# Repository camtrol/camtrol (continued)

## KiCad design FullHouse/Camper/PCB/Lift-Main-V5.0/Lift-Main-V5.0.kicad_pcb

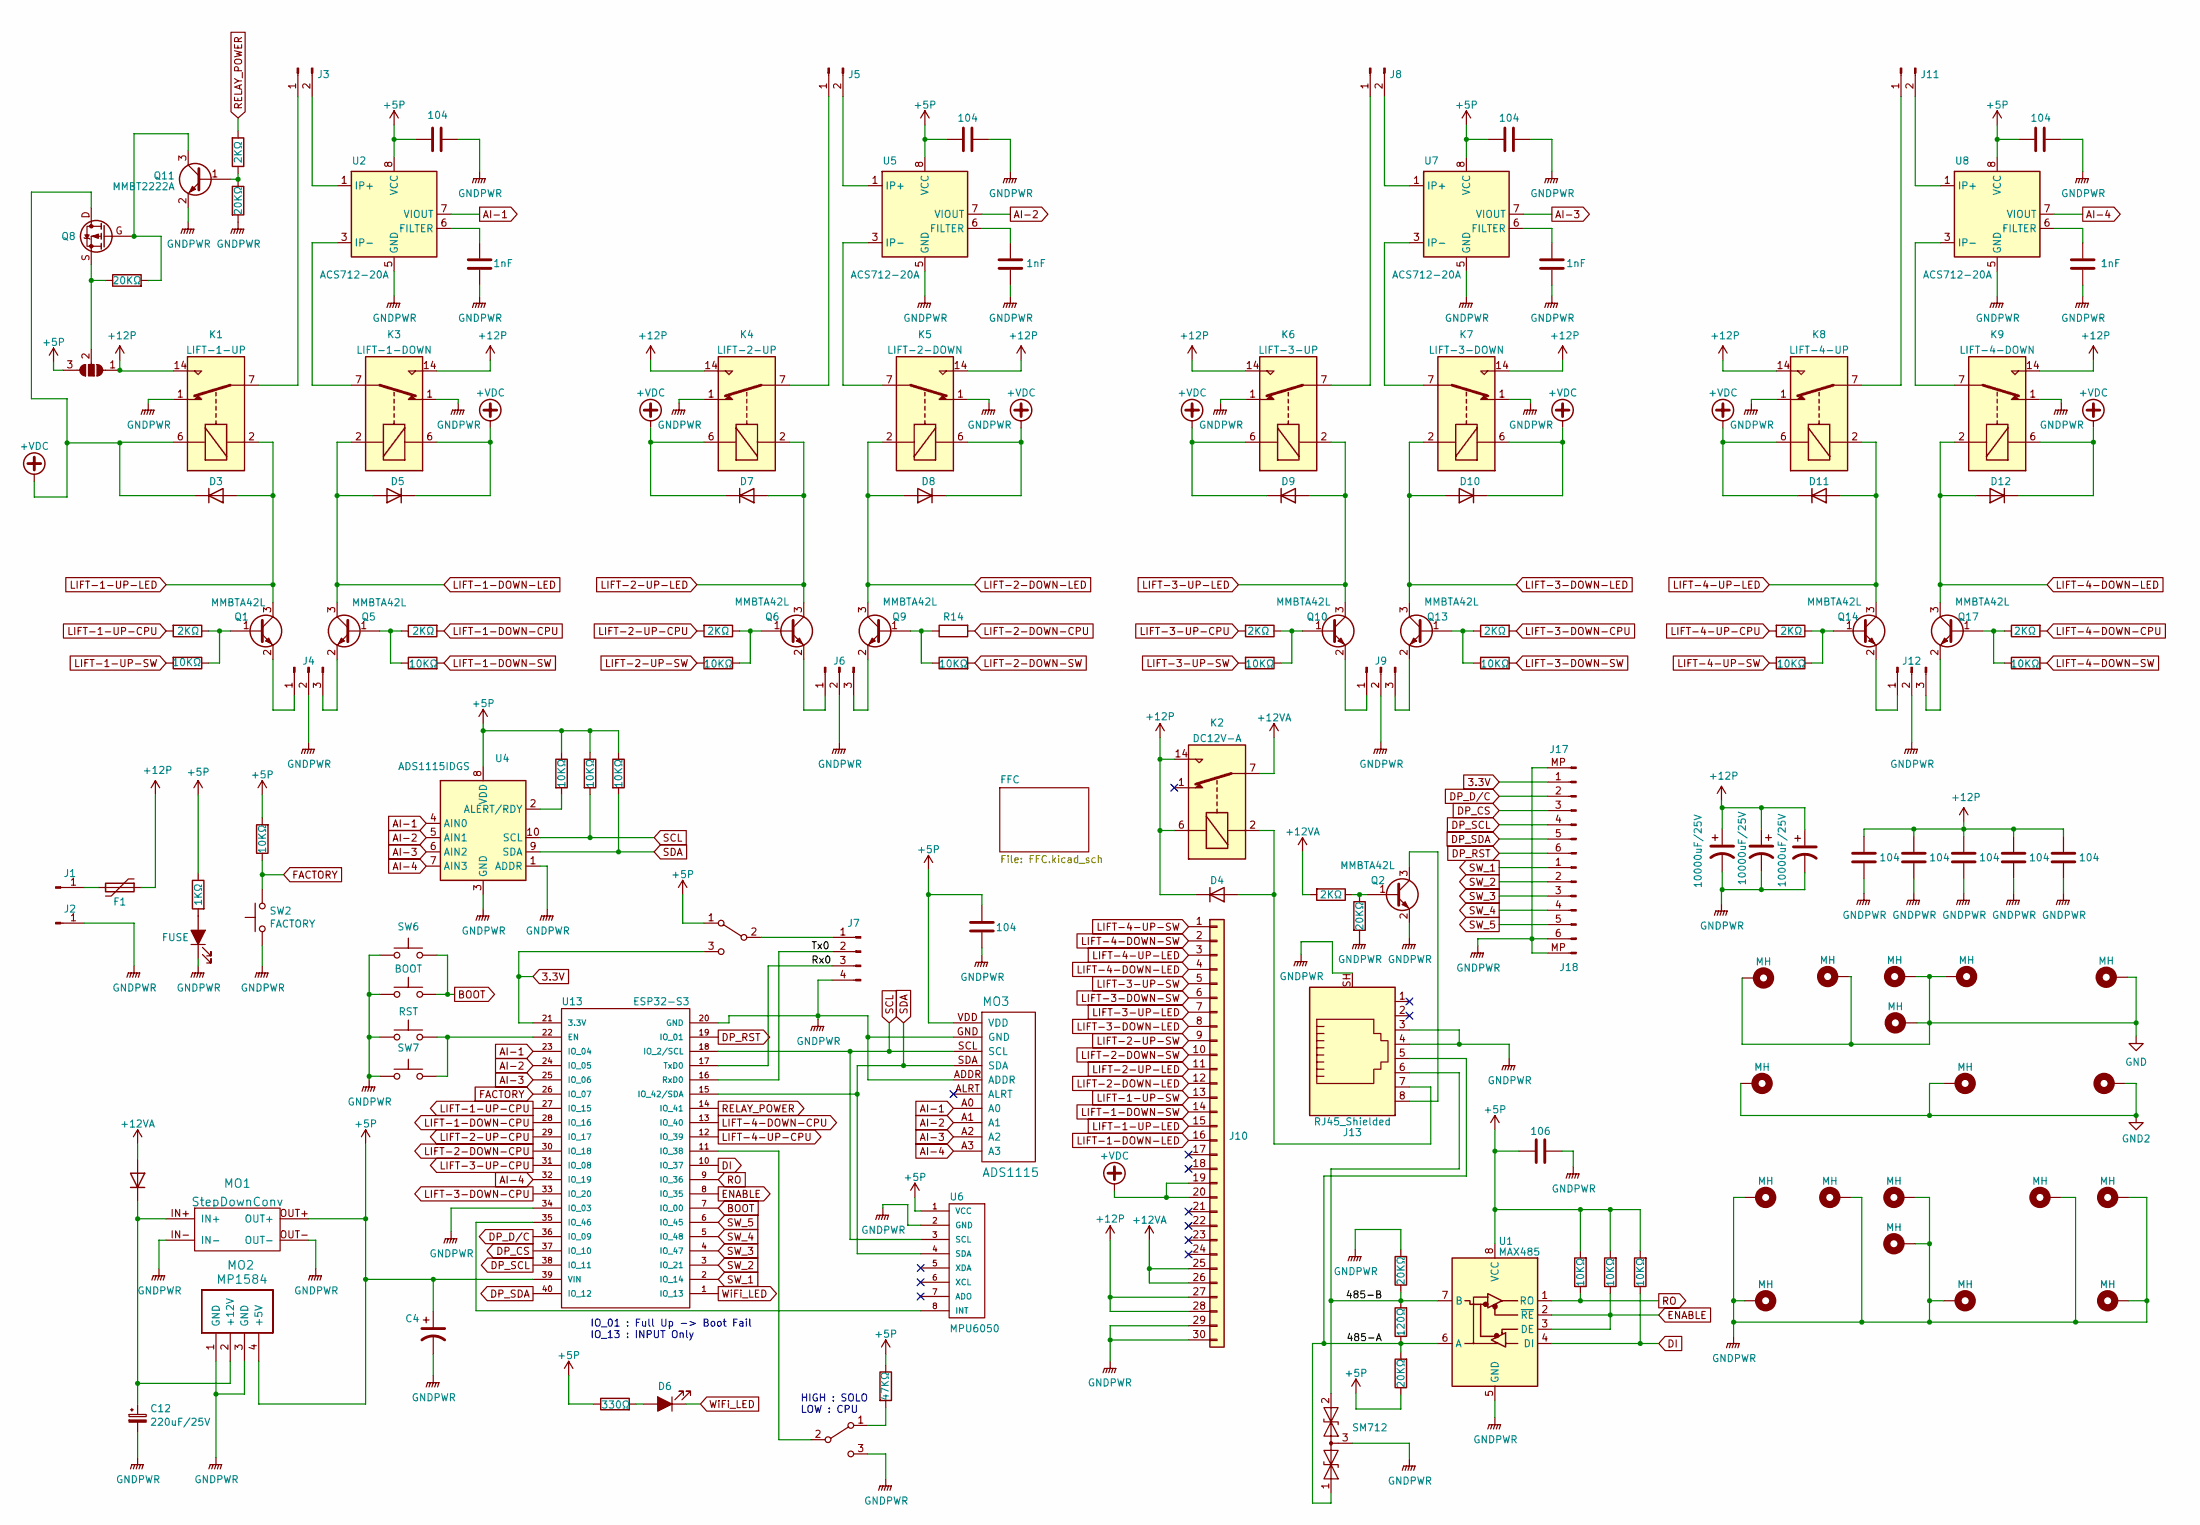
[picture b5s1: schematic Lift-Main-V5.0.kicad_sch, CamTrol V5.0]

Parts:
C2, C5, C6, C8, C11, C13, C14, C15, C16, C17: 104; C_0805_HandSoldering
C3, C7, C9, C19: 1nF; C_0805_HandSoldering
C4: 100uF; CP_Elec_6.3x5.3
C10, C18, C20: 10000uF/25V; CP_Radial_D18.0mm_P7mm
C12: 220uF/25V; CP_Radial_D8.0mm_P2.50mm
C21: 106; C_0805_HandSoldering
D1: SS34; D_SMA
D2: FUSE; LED_0805
D3, D5, D7, D8, D9, D10, D11, D12: type="D" model="1N4148W" lib=""; D_SOD-123
D4: 1N4148W; D_SOD-123
D6: RED LED; LED_0805
D13: SM712; SOT-23
F1: FRG500-16F; FUSE-PIN-Holder
H1, H3, H4, H5, H6, H9, H10, H11, H13, H15, H16, H17, H18, H19, H20, H22, H24, H25: MH; MountingHole_3.2mm_M3-support
J1, J2: BR-120
J3, J5, J8, J11: Conn_01x02_Male; BR-1300C-2P
J4, J6, J9, J12: Conn_01x03_Male; USL-5SAB2-3P
J7: 5267-04P; Molex_SPOX_5267-04A_1x04_P2.50mm_Vertical
J10: Conn_01x30; IDC-Header_2x15_P2.54mm_Vertical
J13: RJ45_Shielded; RJ45_8P_OPEN
J17, J18: Conn_01x06_Pin; JST_GH_SM06B-GHS-TB_1x06-1MP_P1.25mm_Horizontal
JP2: SolderJumper_3_Open; SolderJumper-3_P1.3mm_Open_RoundedPad1.0x1.5mm
K1: LIFT-1-UP; JQC-T78-DC12V-C
K2: DC12V-A; JQC-T78-DC12V-C
K3: LIFT-1-DOWN; JQC-T78-DC12V-C
K4: LIFT-2-UP; JQC-T78-DC12V-C
K5: LIFT-2-DOWN; JQC-T78-DC12V-C
K6: LIFT-3-UP; JQC-T78-DC12V-C
K7: LIFT-3-DOWN; JQC-T78-DC12V-C
K8: LIFT-4-UP; JQC-T78-DC12V-C
K9: LIFT-4-DOWN; JQC-T78-DC12V-C
MO1: StepDownConv; LM2596 DC-DC
MO2: MP1584; MP1584-SMD
MO3: ADS1115
Q1, Q2, Q5, Q6, Q9, Q10, Q13, Q14, Q17: MMBTA42L; SOT-23
Q8: AOD4185; AOD1485
Q11: MMBT2222A; SOT-23
R1, R5, R9, R12, R13, R15, R16, R18, R20, R22, R23, R25, R26, R28, R29: 10KΩ; R_0805_HandSoldering
R2, R7, R11, R17, R21, R24, R27, R30, R38: 2KΩ; R_0805_HandSoldering
R3, R14: 1KΩ; R_0805_HandSoldering
R4, R8, R31, R36, R37: 20KΩ; R_0805_HandSoldering
R6: 120Ω; R_0805_HandSoldering
R10: 330Ω; R_0805_HandSoldering
R19: 47KΩ; R_0805_HandSoldering
SW1, SW3: NW3-SK-02
SW2: FACTORY; SW_Tactile_SKHH_Angled
SW4: RST; SW_SPST_CK_RS282G05A3
SW5: BOOT; SW_SPST_CK_RS282G05A3
SW6, SW7: SW_Push; TS-3404
U1: MAX485; SOIC-8_3.9x4.9mm_P1.27mm
U2, U5, U7, U8: ACS712-20A; SOIC-8_3.9x4.9mm_P1.27mm
U4: ADS1115IDGS; TSSOP-10_3x3mm_P0.5mm
U6: MPU6050
U13: ESP32-S3

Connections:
3.3V: J17.1 (Pin_2), SW3.3 (C), U13.21 (3.3V)
+5P: C2.1, C4.1, C5.2, C6.1, C8.1, C16.1, C21.1, JP2.3 (B), MO1.OUT+, MO2.4 (+5V), MO3.VDD, R1.1, R3.1, R8.1, R9.2, R10.1, R12.2, R13.2, R15.1, R19.1, R28.2, R29.1, SW3.1 (A), U1.8 (VCC), U2.8 (VCC), U4.8 (VDD), U5.8 (VCC), U6.1 (VCC), U7.8 (VCC), U8.8 (VCC), U13.39 (VIN); also elsewhere on the board
+12P: C10.1, C11.1, C13.1, C14.1, C15.1, C17.1, C18.1, C20.1, D4.2 (K), F1.1, J10.27, J10.28, JP2.1 (A), K1.14, K2.6, K2.14, K3.14, K4.14, K5.14, K6.14, K7.14, K8.14, K9.14; also elsewhere on the board
+12VA: D1.1 (A), J10.25, J10.26, K2.7, R30.2; also elsewhere on the board
+VDC: D3.2 (K), D5.2 (K), D7.2 (K), D8.2 (K), D9.2 (K), D10.2 (K), D11.2 (K), D12.2 (K), J10.19, J10.20, K1.6, K3.6, K4.6, K5.6, K6.6, K7.6, K8.6, K9.6, Q8.D (Drain); also elsewhere on the board
/485-A: D13.1 (A1), J13.5, R6.1, R8.2, U1.6 (A)
/485-B: D13.2 (A2), J13.6, R4.1, R6.2, U1.7 (B)
/Rx0: J7.3, U13.17 (TxD0)
/Tx0: J7.2, U13.16 (RxD0)
AI-1: MO3.A0, U2.7 (VIOUT), U4.4 (AIN0), U13.23 (IO_04); also elsewhere on the board
AI-2: MO3.A1, U4.5 (AIN1), U5.7 (VIOUT), U13.24 (IO_05); also elsewhere on the board
AI-3: MO3.A2, U4.6 (AIN2), U7.7 (VIOUT), U13.25 (IO_06); also elsewhere on the board
AI-4: MO3.A3, U4.7 (AIN3), U8.7 (VIOUT), U13.32 (IO_19); also elsewhere on the board
BOOT: SW5.2, SW6.2, U13.7 (IO_00)
DI: R13.1, U1.4 (DI), U13.10 (IO_37)
DP_CS: J17.3 (Pin_4), U13.37 (IO_10)
DP_D/C: J17.2 (Pin_3), U13.36 (IO_09)
DP_RST: J17.6 (Pin_7), U13.19 (IO_01)
DP_SCL: J17.4 (Pin_5), U13.38 (IO_11)
DP_SDA: J17.5 (Pin_6), U13.40 (IO_12)
ENABLE: R12.1, U1.2 (~RE), U1.3 (DE), U13.8 (IO_35)
FACTORY: R28.1, SW2.1, U13.26 (IO_07)
GND: H15.1, H16.1, H17.1, H18.1, H22.1, H24.1
GND2: H13.1, H20.1, H25.1
GNDPWR: C2.2, C3.2, C4.2, C5.1, C6.2, C7.2, C8.2, C9.2, C10.2, C11.2, C12.2, C13.2, C14.2, C15.2, C16.2, C17.2, C18.2, C19.2, C20.2, C21.2, D2.1 (K), D13.3 (common), H1.1, H3.1, H4.1, H5.1, H6.1, H9.1, H10.1, H11.1, H19.1, J2.1, J4.2, J6.2, J7.4, J9.2, J10.29, J10.30, J12.2, J13.3, J13.4, J13.SH, J17.MP (Pin_1), J18.6, J18.MP (Pin_7), K1.1, K3.1, K4.1, K5.1, K6.1, K7.1, K8.1, K9.1, MO1.IN-, MO1.OUT-, MO2.1 (GND), MO2.3 (GND), MO3.ADDR, MO3.GND, Q2.2 (E), Q11.2 (E), R4.2, R31.2, R37.2, SW1.3 (C), SW2.2, SW4.2, SW5.1, SW6.1, SW7.1, U1.5 (GND), U2.5 (GND), U4.1 (ADDR), U4.3 (GND), U5.5 (GND), U6.2 (GND), U7.5 (GND), U8.5 (GND), U13.20 (GND), U13.34 (IO_03); also elsewhere on the board
LIFT-1-DOWN-CPU: R7.2, U13.28 (IO_16)
LIFT-1-DOWN-LED: D5.1 (A), J10.16, K3.2, Q5.3 (C); also elsewhere on the board
LIFT-1-DOWN-SW: J10.14, R16.2; also elsewhere on the board
LIFT-1-UP-CPU: R2.2, U13.27 (IO_15)
LIFT-1-UP-LED: D3.1 (A), J10.15, K1.2, Q1.3 (C); also elsewhere on the board
LIFT-1-UP-SW: J10.13, R5.2; also elsewhere on the board
LIFT-2-DOWN-CPU: R14.2, U13.30 (IO_18)
LIFT-2-DOWN-LED: D8.1 (A), J10.12, K5.2, Q9.3 (C); also elsewhere on the board
LIFT-2-DOWN-SW: J10.10, R20.2; also elsewhere on the board
LIFT-2-UP-CPU: R11.2, U13.29 (IO_17)
LIFT-2-UP-LED: D7.1 (A), J10.11, K4.2, Q6.3 (C); also elsewhere on the board
LIFT-2-UP-SW: J10.9, R18.2; also elsewhere on the board
LIFT-3-DOWN-CPU: R21.2, U13.33 (IO_20)
LIFT-3-DOWN-LED: D10.1 (A), J10.8, K7.2, Q13.3 (C); also elsewhere on the board
LIFT-3-DOWN-SW: J10.6, R23.2; also elsewhere on the board
LIFT-3-UP-CPU: R17.2, U13.31 (IO_08)
LIFT-3-UP-LED: D9.1 (A), J10.7, K6.2, Q10.3 (C); also elsewhere on the board
LIFT-3-UP-SW: J10.5, R22.2; also elsewhere on the board
LIFT-4-DOWN-CPU: R27.2, U13.13 (IO_40)
LIFT-4-DOWN-LED: D12.1 (A), J10.4, K9.2, Q17.3 (C); also elsewhere on the board
LIFT-4-DOWN-SW: J10.2, R26.2; also elsewhere on the board
LIFT-4-UP-CPU: R24.2, U13.12 (IO_39)
LIFT-4-UP-LED: D11.1 (A), J10.3, K8.2, Q14.3 (C); also elsewhere on the board
LIFT-4-UP-SW: J10.1, R25.2; also elsewhere on the board
unnamed: C12.1, D1.2 (K), MO1.IN+, MO2.2 (+12V)
unnamed: D2.2 (A), R3.2
unnamed: D4.1 (A), J13.7, K2.2
unnamed: D6.2 (A), R10.2
unnamed: F1.2, J1.1
unnamed: J3.1, K1.7
unnamed: J3.2, U2.1 (IP+), U2.2 (IP+)
unnamed: J4.1, Q1.2 (E)
unnamed: J4.3, Q5.2 (E)
unnamed: J5.1, K4.7
unnamed: J5.2, U5.1 (IP+), U5.2 (IP+)
unnamed: J6.1, Q6.2 (E)
unnamed: J6.3, Q9.2 (E)
unnamed: J7.1, SW3.2 (B)
unnamed: J8.1, K6.7
unnamed: J8.2, U7.1 (IP+), U7.2 (IP+)
unnamed: J9.1, Q10.2 (E)
unnamed: J9.3, Q13.2 (E)
unnamed: J11.1, K8.7
unnamed: J11.2, U8.1 (IP+), U8.2 (IP+)
unnamed: J12.1, Q14.2 (E)
unnamed: J12.3, Q17.2 (E)
unnamed: JP2.2 (C), Q8.S (Source), R36.1
unnamed: K3.7, U2.3 (IP-), U2.4 (IP-)
unnamed: K5.7, U5.3 (IP-), U5.4 (IP-)
unnamed: K7.7, U7.3 (IP-), U7.4 (IP-)
unnamed: K9.7, U8.3 (IP-), U8.4 (IP-)
unnamed: Q1.1 (B), R2.1, R5.1
unnamed: Q2.1 (B), R30.1, R31.1
unnamed: J13.8, Q2.3 (C)
unnamed: Q5.1 (B), R7.1, R16.1
unnamed: Q6.1 (B), R11.1, R18.1
unnamed: Q9.1 (B), R14.1, R20.1
unnamed: Q10.1 (B), R17.1, R22.1
unnamed: Q11.1 (B), R37.1, R38.1
unnamed: Q8.G (Gate), Q11.3 (C), R36.2
unnamed: Q13.1 (B), R21.1, R23.1
unnamed: Q14.1 (B), R24.1, R25.1
unnamed: Q17.1 (B), R26.1, R27.1
unnamed: R19.2, SW1.1 (A)
unnamed: SW1.2 (B), U13.11 (IO_38)
unnamed: C3.1, U2.6 (FILTER)
unnamed: R1.2, U4.2 (ALERT/RDY)
unnamed: C7.1, U5.6 (FILTER)
unnamed: C9.1, U7.6 (FILTER)
unnamed: C19.1, U8.6 (FILTER)
unnamed: SW4.1, SW7.2, U13.22 (EN)
unnamed: U6.8 (INT), U13.35 (IO_46)
RELAY_POWER: R38.2, U13.14 (IO_41)
RO: R9.1, U1.1 (RO), U13.9 (IO_36)
SCL: MO3.SCL, R15.2, U4.10 (SCL), U6.3 (SCL), U13.18 (IO_2/SCL); also elsewhere on the board
SDA: MO3.SDA, R29.2, U4.9 (SDA), U6.4 (SDA), U13.15 (IO_42/SDA); also elsewhere on the board
SW_1: J18.1, U13.2 (IO_14)
SW_2: J18.2, U13.3 (IO_21)
SW_3: J18.3, U13.4 (IO_47)
SW_4: J18.4, U13.5 (IO_48)
SW_5: J18.5, U13.6 (IO_45)
WiFi_LED: D6.1 (K), U13.1 (IO_13)

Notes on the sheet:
IO_01 : Full Up -> Boot Fail IO_13 : INPUT Only
HIGH : SOLO LOW : CPU

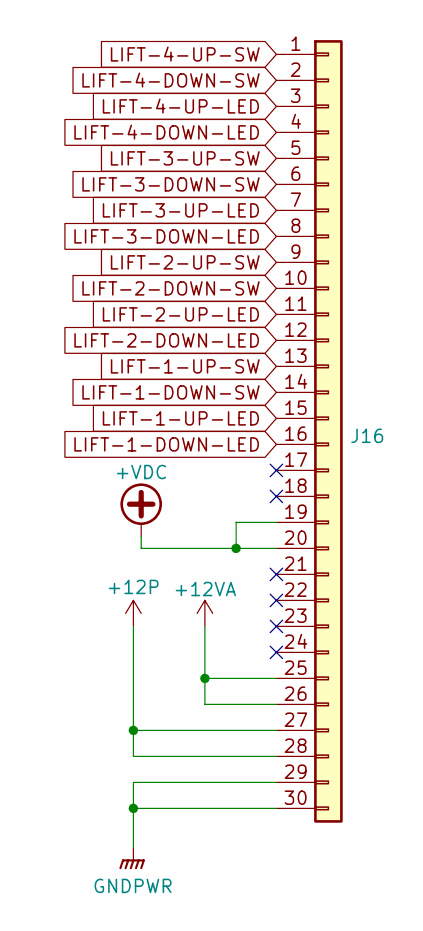
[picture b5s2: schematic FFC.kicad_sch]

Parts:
J16: Conn_01x30; Hirose_FH12-30S-0.5SH_1x30-1MP_P0.50mm_Horizontal

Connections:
+12P: J16.27, J16.28; also elsewhere on the board
+12VA: J16.25, J16.26; also elsewhere on the board
+VDC: J16.19, J16.20; also elsewhere on the board
GNDPWR: J16.29, J16.30; also elsewhere on the board
LIFT-1-DOWN-LED: J16.16; also elsewhere on the board
LIFT-1-DOWN-SW: J16.14; also elsewhere on the board
LIFT-1-UP-LED: J16.15; also elsewhere on the board
LIFT-1-UP-SW: J16.13; also elsewhere on the board
LIFT-2-DOWN-LED: J16.12; also elsewhere on the board
LIFT-2-DOWN-SW: J16.10; also elsewhere on the board
LIFT-2-UP-LED: J16.11; also elsewhere on the board
LIFT-2-UP-SW: J16.9; also elsewhere on the board
LIFT-3-DOWN-LED: J16.8; also elsewhere on the board
LIFT-3-DOWN-SW: J16.6; also elsewhere on the board
LIFT-3-UP-LED: J16.7; also elsewhere on the board
LIFT-3-UP-SW: J16.5; also elsewhere on the board
LIFT-4-DOWN-LED: J16.4; also elsewhere on the board
LIFT-4-DOWN-SW: J16.2; also elsewhere on the board
LIFT-4-UP-LED: J16.3; also elsewhere on the board
LIFT-4-UP-SW: J16.1; also elsewhere on the board

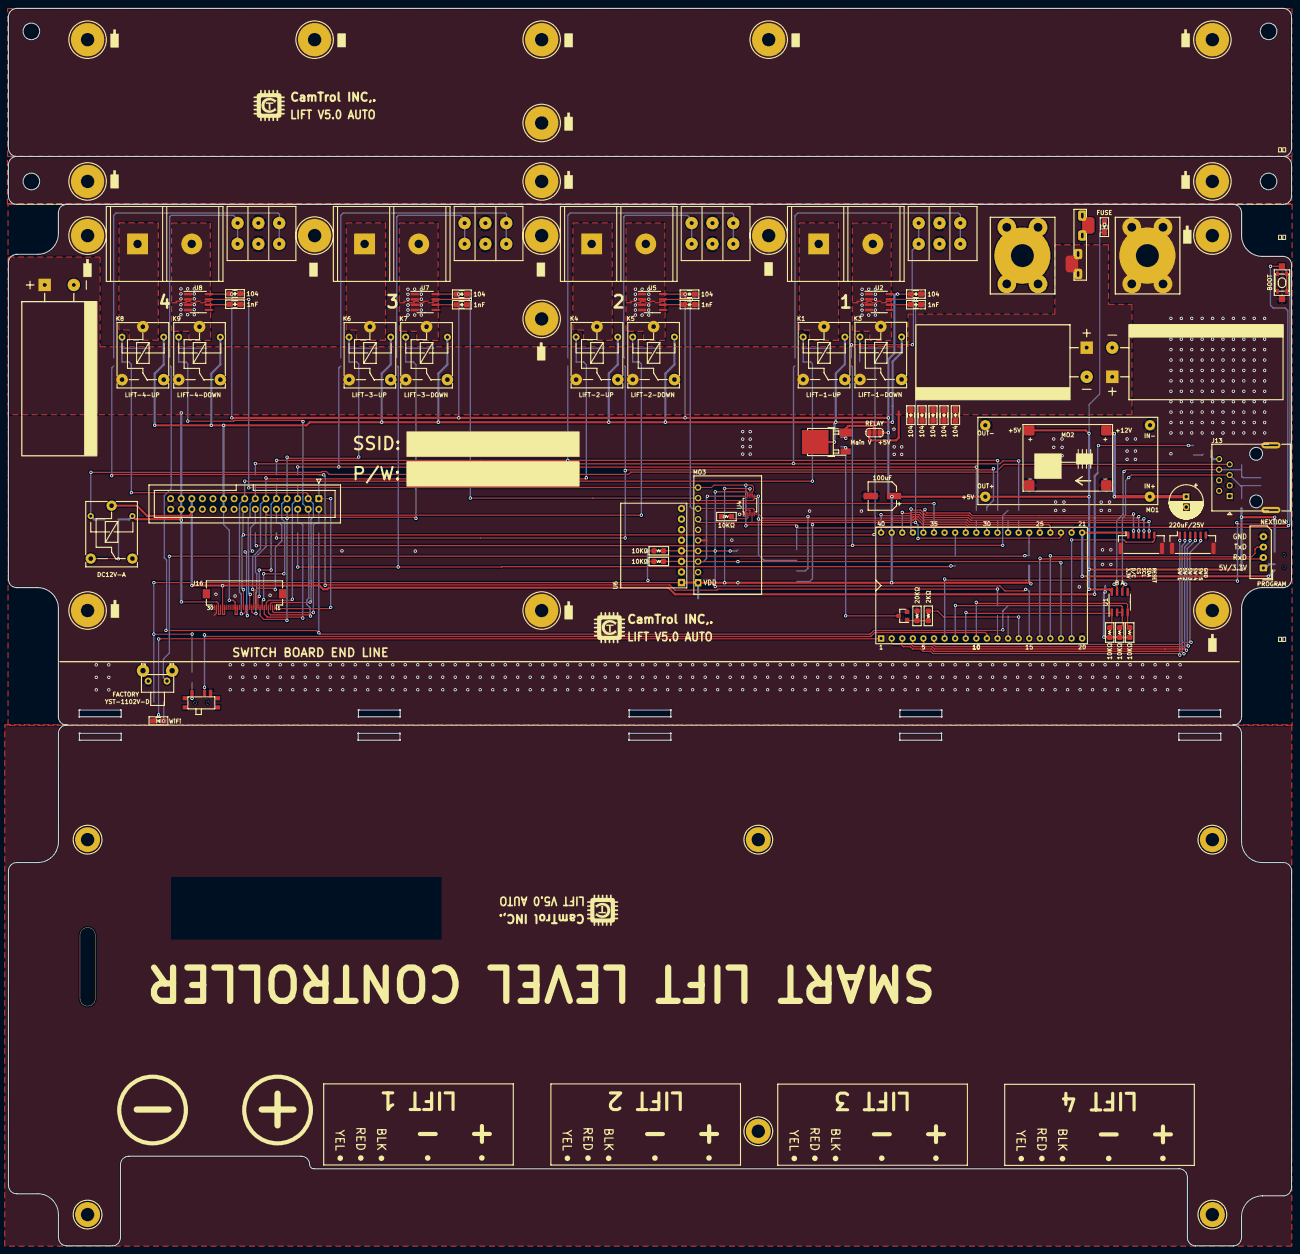
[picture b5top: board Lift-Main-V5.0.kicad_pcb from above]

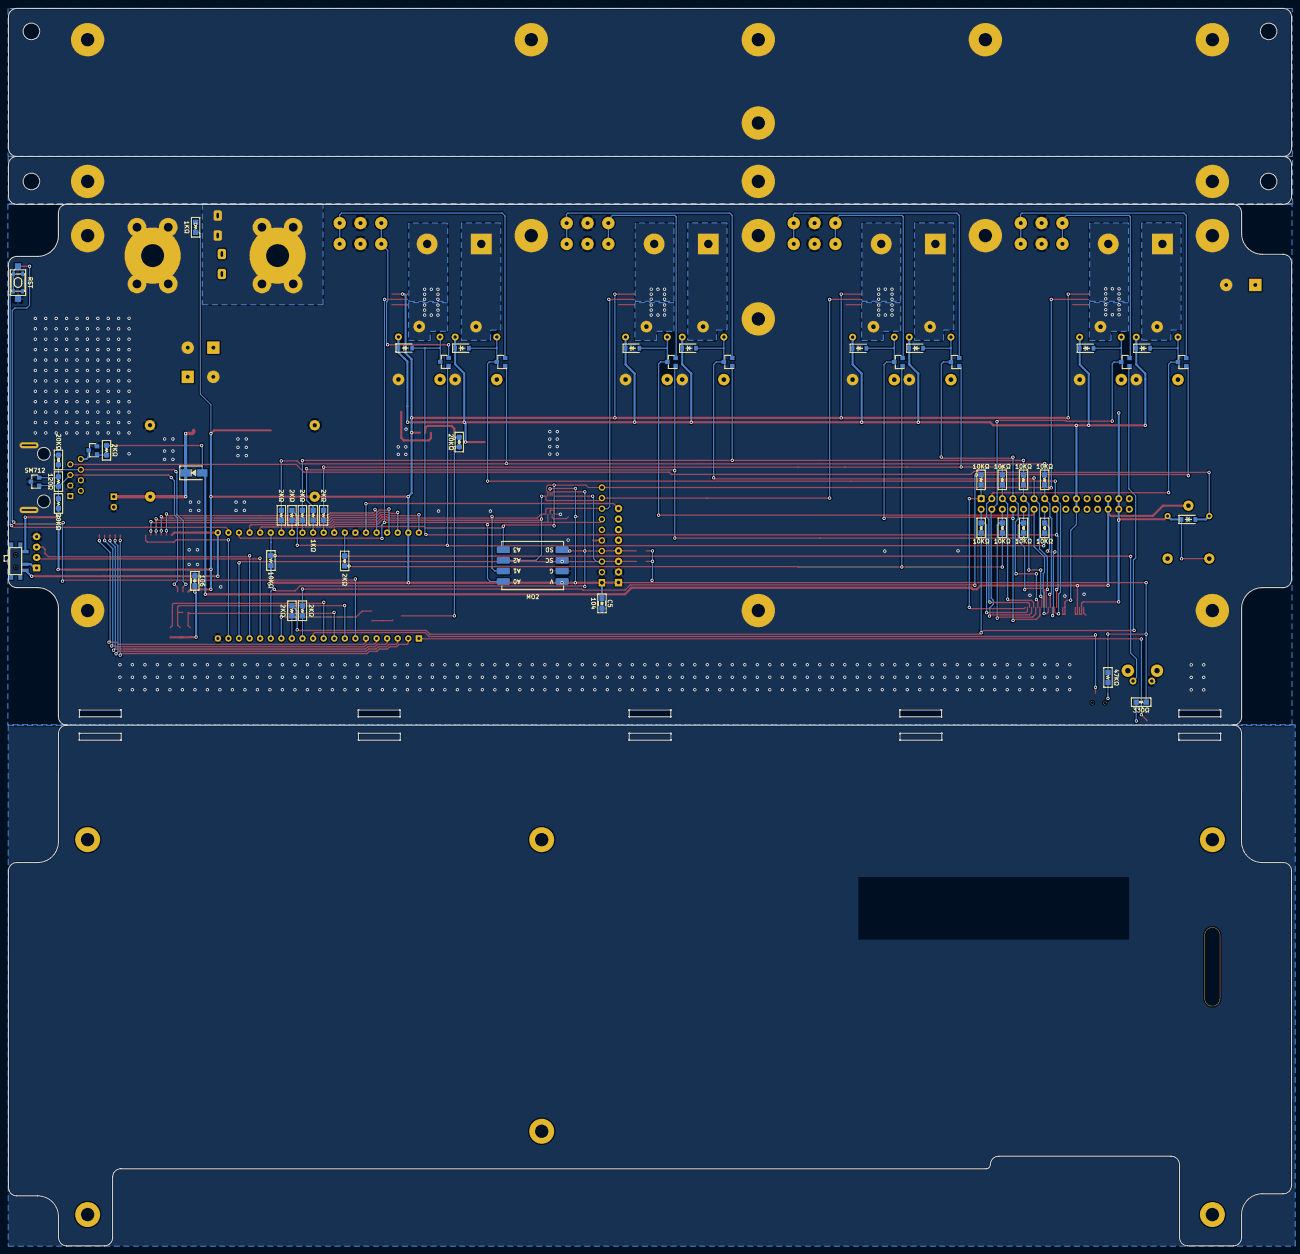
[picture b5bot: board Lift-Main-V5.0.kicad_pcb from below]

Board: 2 copper layers, 308.0 x 297.0 mm, 147 parts (51 on the bottom side), 107 nets.

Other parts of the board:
H1#2, H5#2, H7, H11#2: MH; MountingHole_3.2mm_M3-pcb
H4#2, H10#2: MH; MountingHole_3.2mm_M3-support
MO2#2: ADS1115_SMD

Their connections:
+5P: MO2#2.VCC; also elsewhere on the board
AI-1: MO2#2.A0; also elsewhere on the board
AI-2: MO2#2.A1; also elsewhere on the board
AI-3: MO2#2.A2; also elsewhere on the board
AI-4: MO2#2.A3; also elsewhere on the board
GNDPWR: H4#2.1, H10#2.1, MO2#2.GND; also elsewhere on the board
SCL: MO2#2.SCL; also elsewhere on the board
SDA: MO2#2.SDA; also elsewhere on the board

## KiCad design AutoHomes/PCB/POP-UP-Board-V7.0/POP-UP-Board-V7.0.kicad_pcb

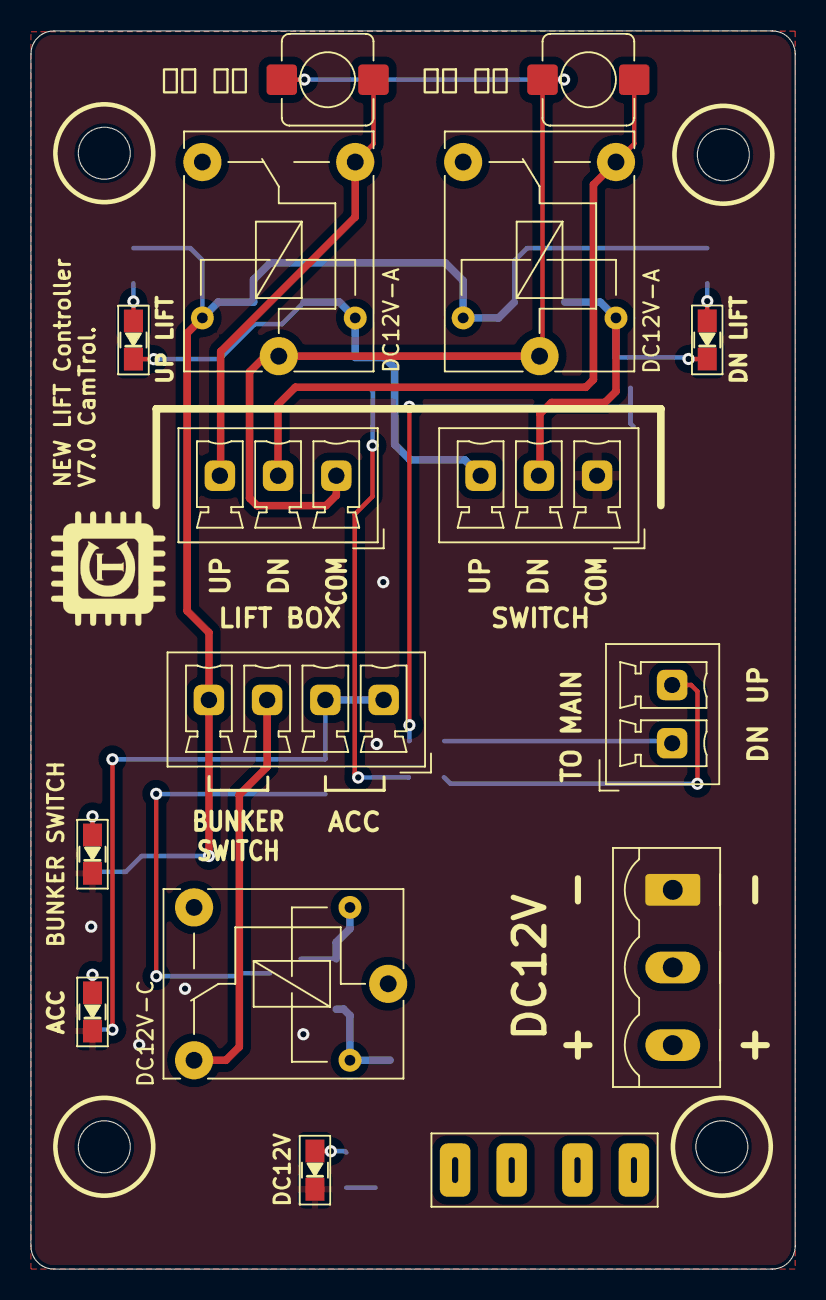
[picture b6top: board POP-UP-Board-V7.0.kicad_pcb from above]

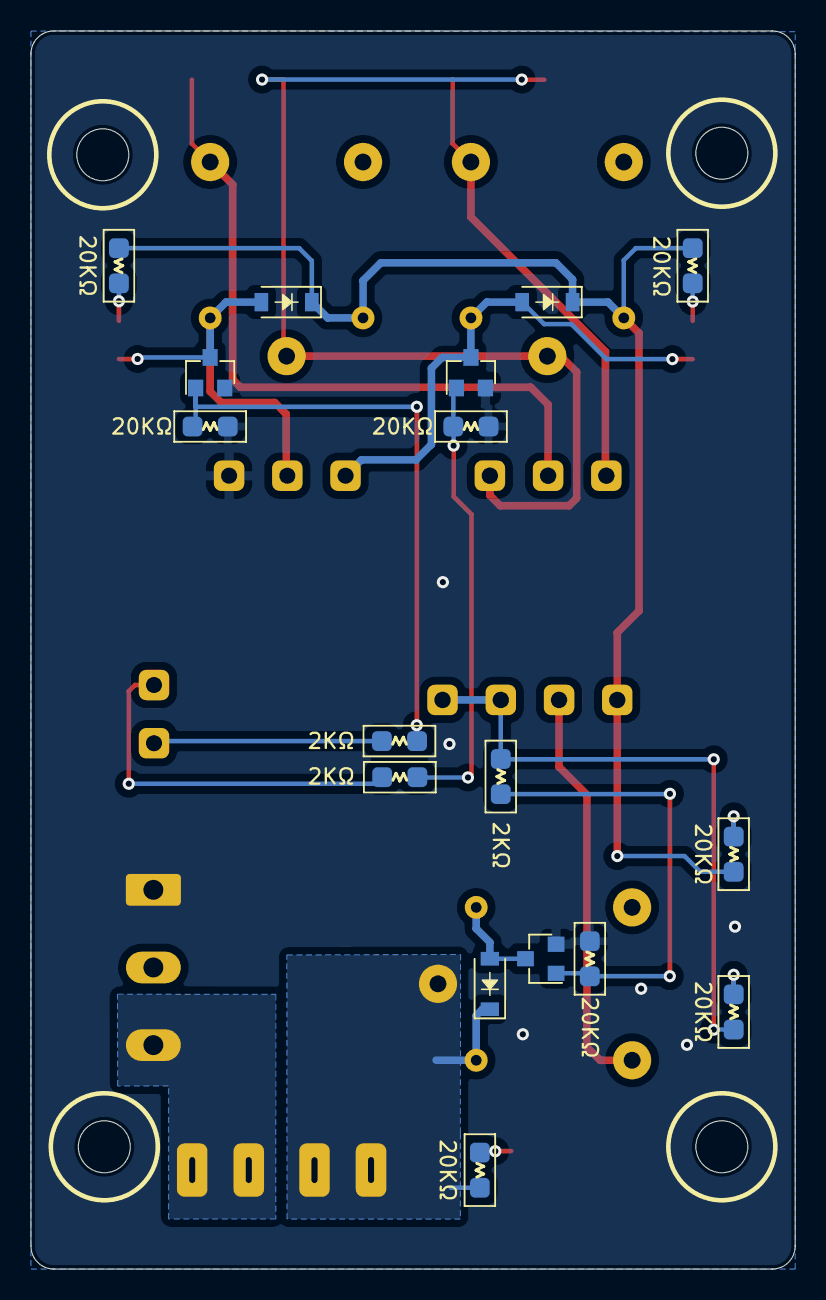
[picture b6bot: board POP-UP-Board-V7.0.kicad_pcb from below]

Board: 2 copper layers, 50.0 x 81.0 mm, 33 parts (17 on the bottom side), 22 nets.

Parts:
D1: BUNKER SWITCH; LED_0805
D2: DC12V; LED_0805
D12, D13, D16: 1N4148W; D_SOD-123
D17: ACC; LED_0805
D20: UP LIFT; LED_0805
D22: DN LIFT; LED_0805
F2: FRG500-16F; FUSE-PIN-Holder-Mini
J1: Conn_01x03_Pin; PhoenixContact_MSTBVA_2,5_3-G-5,08_1x03_P5.08mm_Vertical_NEW
J2, J7: Conn_01x03_Male; PhoenixContact_MCV_1,5_3-G-3.81_1x03_P3.81mm_Vertical
J3: Conn_01x02_Pin; PhoenixContact_MCV_1,5_2-G-3.81_1x02_P3.81mm_Vertical
J4: Conn_01x04_Pin; PhoenixContact_MCV_1,5_4-G-3.81_1x04_P3.81mm_Vertical
K5, K6: DC12V; JQC-T78-DC12V-C
K7: JQC-T78-DC5V-A; JQC-T78-DC12V-C
Q1, Q2, Q5: MMBT2222A; SOT-23
R1, R4, R7, R8, R9, R10, R12, R13: 20KΩ; R_0805_HandSoldering
R2, R3, R14: 2KΩ; R_0805_HandSoldering
SW3: 강제 상승; SMD-SW_6x6x5mm
SW4: 강제 하강; SMD-SW_6x6x5mm

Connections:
+12P: D16.2 (K), F2.2, K7.6, K7.7, R4.1
/POPUP DOWN: J3.1, R3.2
/POPUP UP: J3.2, R2.2
GNDPWR: D1.1 (K), D2.1 (K), D17.1 (K), J1.1, J2.1, Q1.2 (E), Q2.2 (E), Q5.2 (E), R7.1, R10.1, R13.2
unnamed: D1.2 (A), R1.2
unnamed: D2.2 (A), R4.2
unnamed: D12.1 (A), D20.1 (K), J2.3, K6.2, Q1.3 (C)
unnamed: D12.2 (K), D13.2 (K), J4.4, K5.6, K6.6, R1.1, R9.1, R12.1
unnamed: D13.1 (A), D22.1 (K), J2.2, K5.2, Q2.3 (C)
unnamed: D16.1 (A), K7.2, Q5.3 (C)
unnamed: D17.2 (A), R8.2
unnamed: D20.2 (A), R9.2
unnamed: D22.2 (A), R12.2
unnamed: F2.1, J1.3
unnamed: J4.1, J4.2, R8.1, R14.2
unnamed: J4.3, K7.1
unnamed: J7.1, K5.7, K6.7, SW3.2, SW4.2
unnamed: J7.2, K5.14, SW4.1
unnamed: J7.3, K6.14, SW3.1
unnamed: Q1.1 (B), R2.1, R7.2
unnamed: Q2.1 (B), R3.1, R10.2
unnamed: Q5.1 (B), R13.1, R14.1

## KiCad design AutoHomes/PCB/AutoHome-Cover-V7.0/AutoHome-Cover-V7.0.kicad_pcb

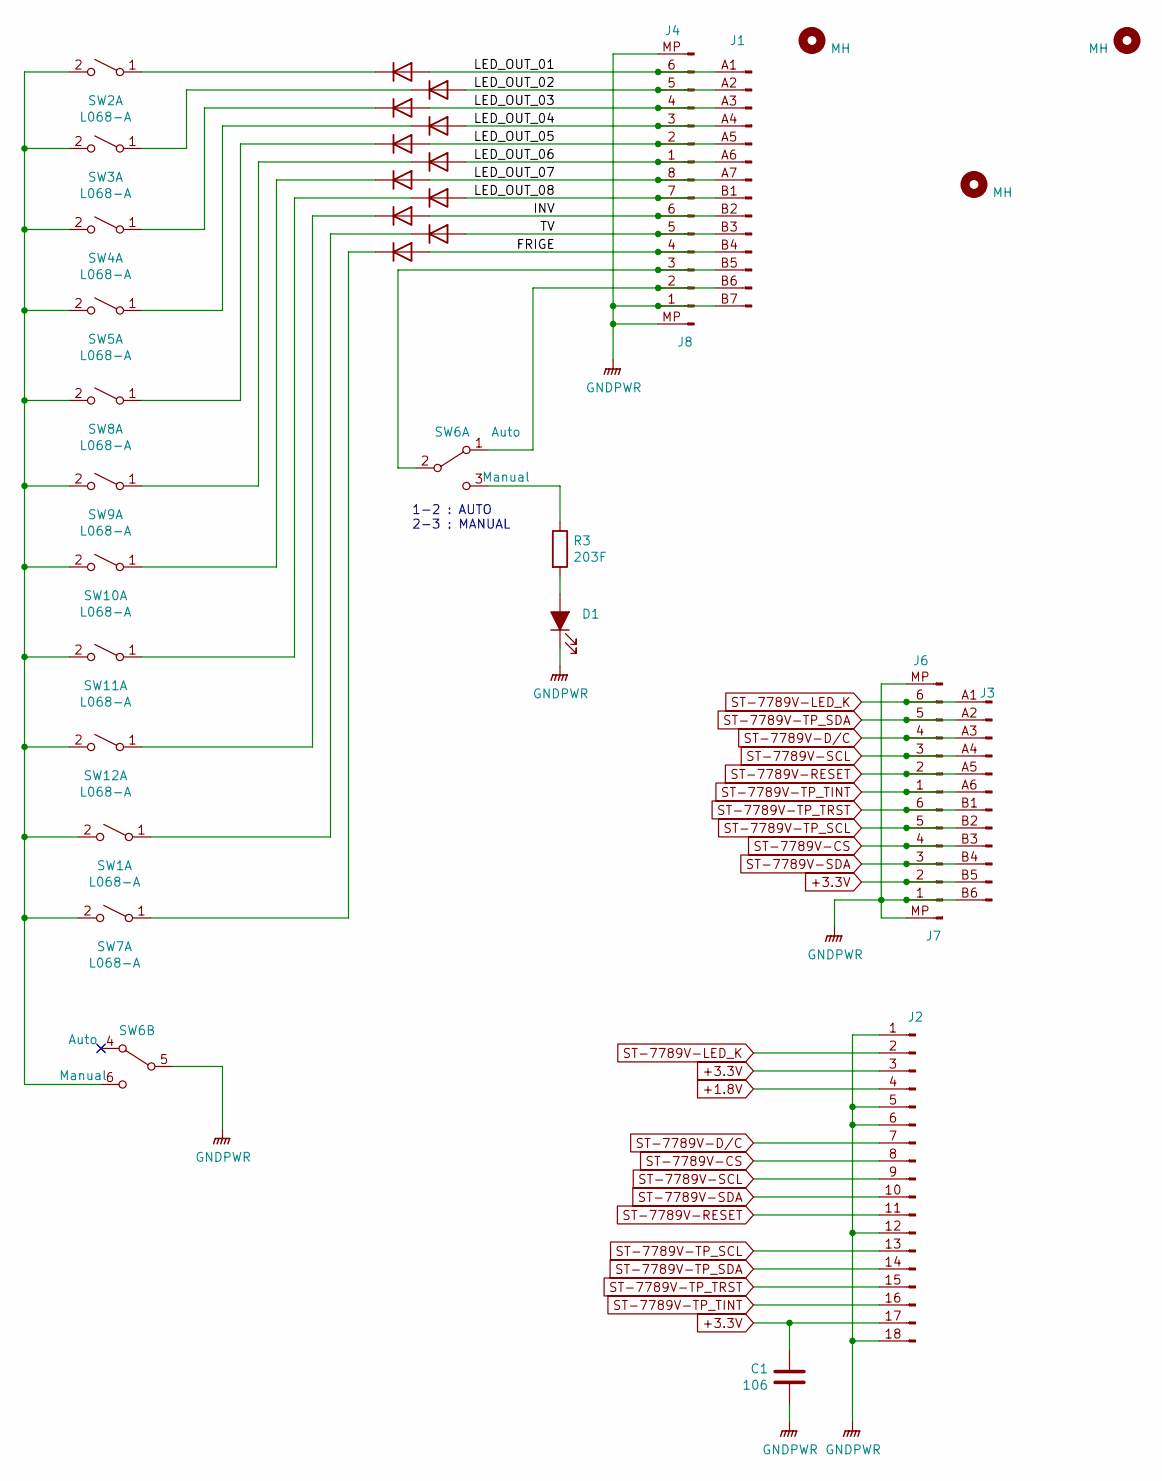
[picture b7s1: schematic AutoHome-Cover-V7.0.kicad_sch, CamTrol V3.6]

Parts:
C1: 106; C_0805_HandSoldering
D1: MANUAL; LED_0805
D2, D3, D4, D5, D6, D7, D12, D13, D14, D15, D16: type="D" model="1N4148W" lib=""; D_SOD-123
H1, H2, H4: MH; MountingHole_3.2mm_M3-pcb
J1: Conn_01x12_Male; SMD_CONN_1x14_P1.270mm
J2: Conn_01x12_Male; Hirose_FH12-18S-0.5SH_1x18-1MP_P0.50mm_Horizontal_ST7789V3-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
J3: Conn_01x12_Male; SMD_CONN_1x12_P1.270mm
J4, J6, J7: Conn_01x06_Pin; JST_GH_SM06B-GHS-TB_1x06-1MP_P1.25mm_Horizontal
J8: Conn_01x08_Pin; JST_GH_SM08B-GHS-TB_1x08-1MP_P1.25mm_Horizontal
R3: 203F; R_0805_HandSoldering
SW1, SW2, SW3, SW4, SW5, SW7, SW8, SW9, SW10, SW11, SW12: L068-A; 8.5x8.5_Push_Lock
SW6: SW_DPDT_x2; YSS-1201

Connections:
+1.8V: J2.4
+3.3V: C1.2, J2.3, J2.17, J3.B5 (Pin_11), J7.2 (Pin_5)
/FRIGE: D7.1 (A), J1.B4 (Pin_8), J8.4 (Pin_5)
/INV: D16.1 (A), J1.B2 (Pin_4), J8.6 (Pin_3)
/LED_OUT_01: D2.1 (A), J1.A1 (Pin_1), J4.6 (Pin_2)
/LED_OUT_02: D3.1 (A), J1.A2 (Pin_3), J4.5 (Pin_3)
/LED_OUT_03: D4.1 (A), J1.A3 (Pin_5), J4.4
/LED_OUT_04: D5.1 (A), J1.A4 (Pin_7), J4.3 (Pin_5)
/LED_OUT_05: D12.1 (A), J1.A5 (Pin_9), J4.2 (Pin_6)
/LED_OUT_06: D13.1 (A), J1.A6 (Pin_11), J4.1 (Pin_7)
/LED_OUT_07: D14.1 (A), J1.A7 (Pin_13), J8.8 (Pin_1)
/LED_OUT_08: D15.1 (A), J1.B1 (Pin_2), J8.7 (Pin_2)
/TV: D6.1 (A), J1.B3 (Pin_6), J8.5 (Pin_4)
GNDPWR: C1.1, D1.1 (K), J1.B7 (Pin_14), J2.1, J2.5, J2.6, J2.12, J2.18, J3.B6 (Pin_12), J4.MP (Pin_1), J6.MP (Pin_1), J7.1 (Pin_6), J7.MP (Pin_7), J8.1 (Pin_8), J8.MP (Pin_9), SW6.5 (B)
unnamed: D1.2 (A), R3.2
unnamed: D2.2 (K), SW2.1 (A)
unnamed: D3.2 (K), SW3.1 (A)
unnamed: D4.2 (K), SW4.1 (A)
unnamed: D5.2 (K), SW5.1 (A)
unnamed: D6.2 (K), SW1.1 (A)
unnamed: D7.2 (K), SW7.1 (A)
unnamed: D12.2 (K), SW8.1 (A)
unnamed: D13.2 (K), SW9.1 (A)
unnamed: D14.2 (K), SW10.1 (A)
unnamed: D15.2 (K), SW11.1 (A)
unnamed: D16.2 (K), SW12.1 (A)
unnamed: J1.B5 (Pin_10), J8.3 (Pin_6), SW6.2 (B)
unnamed: J1.B6 (Pin_12), J8.2 (Pin_7), SW6.1 (A)
unnamed: R3.1, SW6.3 (C)
unnamed: SW1.2 (B), SW2.2 (B), SW3.2 (B), SW4.2 (B), SW5.2 (B), SW6.6 (C), SW7.2 (B), SW8.2 (B), SW9.2 (B), SW10.2 (B), SW11.2 (B), SW12.2 (B)
ST-7789V-CS: J2.8, J3.B3 (Pin_9), J7.4 (Pin_3)
ST-7789V-D/C: J2.7, J3.A3 (Pin_3), J6.4
ST-7789V-LED_K: J2.2, J3.A1 (Pin_1), J6.6 (Pin_2)
ST-7789V-RESET: J2.11, J3.A5 (Pin_5), J6.2 (Pin_6)
ST-7789V-SCL: J2.9, J3.A4 (Pin_4), J6.3 (Pin_5)
ST-7789V-SDA: J2.10, J3.B4 (Pin_10), J7.3 (Pin_4)
ST-7789V-TP_SCL: J2.13, J3.B2 (Pin_8), J7.5 (Pin_2)
ST-7789V-TP_SDA: J2.14, J3.A2 (Pin_2), J6.5 (Pin_3)
ST-7789V-TP_TINT: J2.16, J3.A6 (Pin_6), J6.1 (Pin_7)
ST-7789V-TP_TRST: J2.15, J3.B1 (Pin_7), J7.6 (Pin_1)

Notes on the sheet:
1-2 : AUTO 2-3 : MANUAL

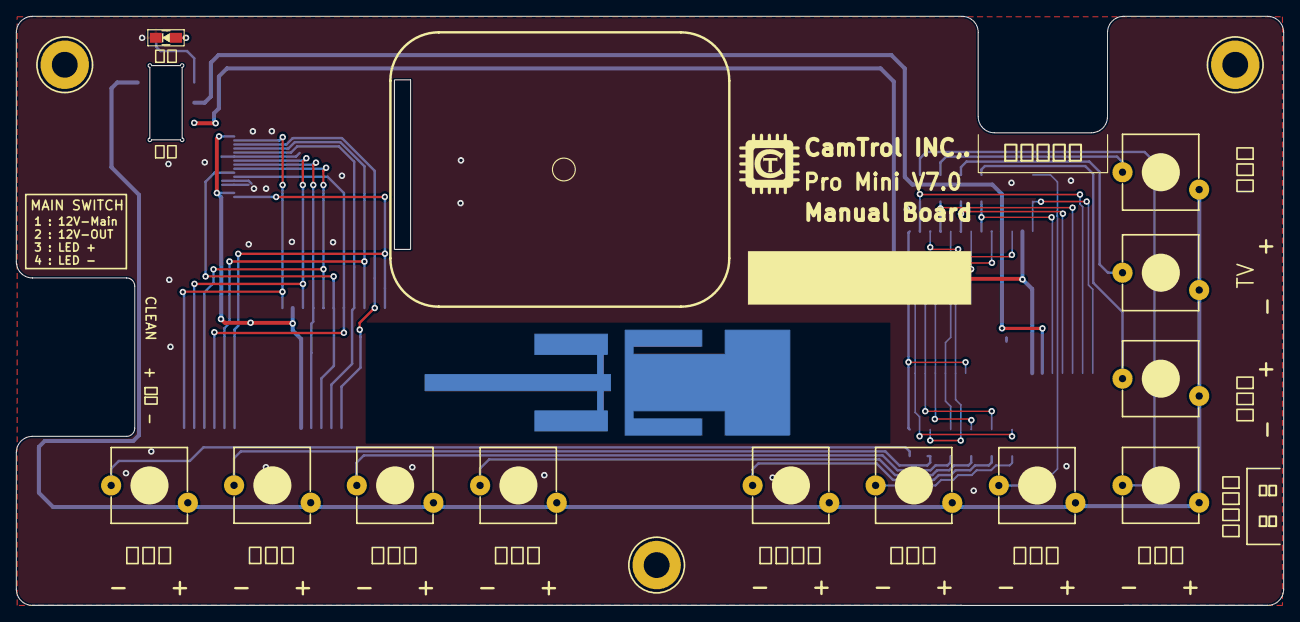
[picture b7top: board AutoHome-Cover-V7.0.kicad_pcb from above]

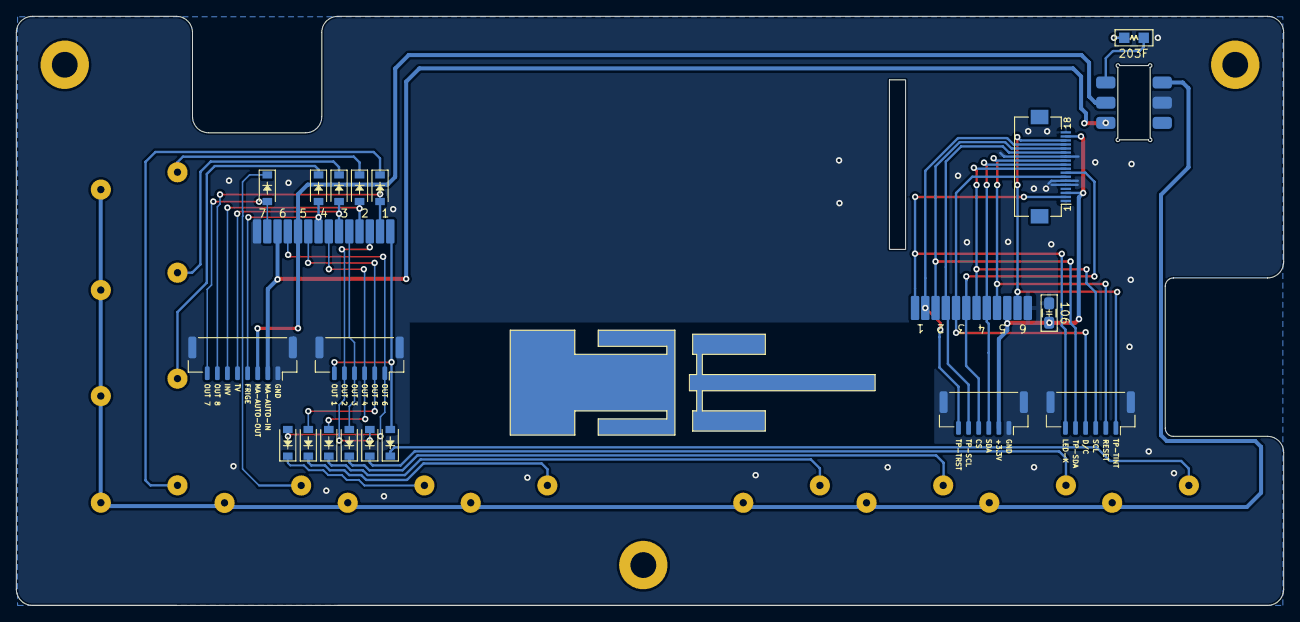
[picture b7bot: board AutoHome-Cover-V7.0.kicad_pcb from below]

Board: 2 copper layers, 157.1 x 73.0 mm, 38 parts (21 on the bottom side), 39 nets.

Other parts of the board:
A1: IPX-ANTENA
U1: 1.3 OLED; ST7789V
